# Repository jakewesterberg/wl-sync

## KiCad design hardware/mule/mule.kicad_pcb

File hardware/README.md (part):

# wl-sync breakout PCB

KiCad sources for the sync-box breakout board: a 2U rack-mount mixed-signal hub that sits
between the behavioural task PC, the sync-box module, the recording NI card, and the Intan RHS
amplifier. Every signal that crosses between those devices terminates on this board, is
conditioned once, and is fanned out — so a rig is reproducible from the board rather than from
hand wiring. "Sync-box module" is deliberately not a single product name: the module carries a
BCM2712 SoC and RP1 I/O controller either way, so its GPIO map and pinout are identical whether
it ships as a Raspberry Pi 5 or as a Compute Module 5 (Lite) on the official CM5 IO Board — the
choice between the two is a floorplan/placement decision this repository's own sources do not
yet lock in, not an electrical one.

Full design rationale, the signal contract, the grounding scheme, and the fabrication schedule
live in [`docs/superpowers/specs/2026-08-13-syncbox-breakout-pcb-design.md`](../docs/superpowers/specs/2026-08-13-syncbox-breakout-pcb-design.md).
The implementation plan (task breakdown, net naming convention, file layout) is at
[`docs/superpowers/plans/2026-08-13-breakout-pcb.md`](../docs/superpowers/plans/2026-08-13-breakout-pcb.md).
This repository is public: documentation here states electrical and mechanical facts and
tooling instructions only, and reproduces no text from either linked document's private source
material.

## Settled facts (record kept here, 2026-08-15)

Three facts a rig operator or firmware author needs and should not have to re-derive from the
schematic or the private spec:

- **The two photodiode comparator channels have distinct, fixed roles.** `A_PD1` watches the
  **task patch** — the stimulus-onset signal a behavioural task draws to cue an event.
  `A_PD2` watches the **flip patch**, a corner region of the display that alternates every
  refresh, making it a frame clock. Both reach the recorders as a digital edge through their
  own comparator (`PD1_COMP`/`PD2_COMP`) as well as an analog copy; the comparator lines carry
  the timing, the analog copies carry waveform and intensity.
- **The default eight analog channels Intan receives** (of the 16 sources this board carries;
  Intan's own ceiling is 8, and which eight is a mux setting, not a copper fact — see the
  ADG1206 mux truth table below): `A_PD1`, `A_EYE_LX`, `A_EYE_LY`, `A_EYE_LP`, `A_JOY_X`,
  `A_JOY_Y`, `A_MIC`, `A_ACC`. One complete eye (left, position + pupil) rather than partial
  data from both; the six eye channels are the first candidates to drop if a different set is
  ever needed, since they have an authoritative record on the eye-tracker PC independent of
  this board — the photodiode, joystick, accelerometer, and microphone channels do not.
- **MonkeyLogic's `RewardPolarity` setting must be `HIGH` to match this board.** This board's
  reward-commanded input (`RWD_CMD`) is active-HIGH by design (idle-LOW, pulses HIGH on
  delivery — the same convention every other event line on this board uses, and the polarity
  the reward-OR gate's own same-polarity structural check assumes and enforces on the
  debounced-button side). `RewardPolarity` is a MonkeyLogic Main Menu setting provided so a
  rig can match relays that trigger on sinking instead — it is a configuration to set for this
  board, never an unknown to discover at commissioning time.

## Two tracks

- **`hardware/mule/`** — the event-path mule. A small, fast board carrying only the 17-line
  event-code path plus one instance of each level-shift and isolation stage the full board
  reuses. It exists to reach the bench while the breakout board is still in layout, so the
  level-shifting and optocoupler topology gets validated against real hardware early enough to
  revise the sheets that depend on it.
- **`hardware/breakout/`** — the breakout board itself. A root sheet plus one hierarchical sheet
  per functional block (power, task-PC digital, Pi interface, analog front end, analog-to-NI,
  mux-to-Intan, comparators, opto-to-NI, opto-to-Intan, USB/I²C control).

As of this commit, `hardware/mule/` carries a generated schematic (`mule.kicad_sch`, produced
by `hardware/gen/gen_mule.py`) and a generated, placed-but-unrouted board (`mule.kicad_pcb`,
produced by `hardware/gen/gen_mule_pcb.py`) — see `hardware/mule/floorplan.md` for the
placement rationale and the constraints a router must respect. `hardware/breakout/` carries
the root sheet (`breakout.kicad_sch`, produced by `hardware/gen/gen_breakout.py`) plus two
populated child sheets so far: `sheets/power.kicad_sch` (produced by
`hardware/gen/gen_breakout_power.py`, Task 7) — the 5-position analog/logic inlet (widened
from 4 pins at Task 7 fix round 1, see below), the +3V3 logic rail regulated from +5V, and
the one isolated ±12V supply the other nine sheets draw power from; see that generator's own
module docstring and `check_breakout_power_netlist.py` for the design and its verification.
Task 7 fix round 1 (task-7-report.md's "Fix round 1") corrected two defects found in
review: the +5V rail was undersized regulating it down from +12V on board (fixed by
bringing +5V in directly from the external supply on a fifth inlet pin instead, budgeted
for 400mA), and the child sheet's own component `(instances (path ...))` ancestor chain was
self-referential rather than the real root+sheet-symbol chain a nested sheet needs (fixed
generically in `kicad_sch.py`, not just for this one sheet — see the "KiCad gotchas" entry
below). Task 7 fix round 2 (task-7-report.md's "Fix round 2") replaced the inlet
**connector** itself — not its electrical design — after a reviewer confirmed the mini-DIN
footprints modelled an evenly-spaced ring the real Same Sky MD-40SN/MD-50SN datasheet's own
diagrams contradict, and that both parts are discontinued besides. The inlet is now a
5-position, IEC 61076-2-101 A-coded, keyed, screw-locking M12 connector (Amphenol LTW
M12A-05PFFP-SF8001, current production, 811 units in stock directly confirmed at DigiKey)
— see "Custom connector footprints" below for the full selection rationale and
per-dimension sourcing.

**Panel-instrumentation task (2026-08-15), Change D — four of the five "things a rack
instrument needs that this one lacked" (spec §9.8) land on this sheet** (the fifth,
the barcode heartbeat LED, is on `pi-interface.kicad_sch` — see that sheet's own
paragraph below):

- **Chassis earth stud (`J56`):** a `Connector_Generic:Conn_01x01` on footprint
  `MountingHole:MountingHole_3.2mm_M3_Pad` — an M3-clearance hole *with* a connected
  copper pad, simultaneously the mechanical mount and the electrical land the
  cage-to-rack bond (spec §5.6) needs somewhere to terminate. Carries a new net,
  `CHASSIS_GND`, joined to `DGND` at exactly one net tie (`NT3`) — mirroring `NT2`'s own
  `FAN_RTN`↔`DGND` treatment exactly, so the stud reaches the board's single star point
  transitively (through `NT3` then `NT1`/`NT2`), never by a second, competing path.
- **Power-good LED per rail (`D40`/`D41`/`D42`, +12V/−12V/+5V):** series resistor + LED
  between each rail and its own local ground reference (`AGND` for ±12V, `DGND` for
  +5V) — `−12V`'s own pair is mirrored (resistor/anode on the `AGND` side, cathode on
  `−12V`), the identical reasoning `D2`'s own reverse-polarity-diode orientation already
  uses. ~4.5 mA target each (`R192`/`R193` = 2.2k, `R194` = 680R) — negligible against
  any rail's own real budget.
- **Rail test points (`TP1`–`TP7`):** one `Connector:TestPoint` per voltage rail (+12V,
  −12V, +5V, +3V3, ISO_P12, ISO_N12) *plus one on `INTAN_GND`* — the isolated domain's
  own reference, without which `ISO_P12`/`ISO_N12` cannot actually be measured at all
  (`INTAN_GND` is galvanically separate from `AGND`/`DGND`, spec §5.3/§5.5). `AGND`/
  `DGND` themselves are not given dedicated test points — already trivially probable at
  any of this sheet's own many ground pads.
- **Main input fusing (`F2`/`F3`/`F4`, +12V/−12V/+5V):** "the fans already have a
  polyfuse; these did not" (spec §9.8). Placed upstream of each rail's own existing
  reverse-polarity diode (`D1`/`D2`/`D3`) — their own raw-side net renamed `*_FUSED`
  (e.g. `P12_RAW` → `F2` → `P12_FUSED` → `D1` → `+12V`), `D1`–`D3` themselves keeping
  their existing references unchanged. `F2`/`F3` are Littelfuse `1206L050/15YR`
  (500 mA hold / 1 A trip / **15 V** max), the same real part as the fan feed's `F1`.

  **`F4` is a different part — finding M7, 2026-08-16.** The sizing note that used to
  sit here called +5V's 1.25× hold margin "tighter than usual but accepted, because a
  main-input fuse guards against a gross fault". That reasoning does not survive finding
  F1: the +5 V rail now carries **392 mA typ / 495 mA max**, and a `1206L050` holds only
  ~0.44 A at this chassis's 35 °C ambient. It would have tripped in **normal operation**,
  not on a fault. `F4` is now **`1206L110-C`** — 1.10 A hold / 2.20 A trip, ~0.97 A
  derated at 35 °C, a 1.97× margin.

  **Its V_max is 6 Vdc, not 15, and that is not interchangeable.** In the 1206L series
  the elevated-voltage variants exist only at the two lowest hold currents; everything at
  0.75 A and above is a +5 V-rail part. So `F4` could move and `F1`/`F2`/`F3` cannot —
  **0.50 A is the largest 1206L hold current available to a 12 V rail at all**, which is
  also why M7's "0.75 A recommended" for the fan feed cannot be satisfied in this series.
  Do not consolidate the two values back into one.

- **The fan branch is parallel to the main +12 V branch, not downstream of it (finding
  F7, 2026-08-16).** `F1` used to be fed from `+12V`, which put it in series with `F2` at
  identical ratings — and two identical parts in series have no selectivity at all: a fan
  fault at 0.9 A is below `F1`'s trip but over `F2`'s hold, so **`F2` could open first and
  kill the analog rails to protect the fans.** The fan feed now taps `P12_RAW` directly,
  with its own reverse-polarity Schottky (`D44`, `SS14`) since it no longer sits behind
  `D1`:

  ```
  J1.1 → P12_RAW ─┬─ [F2] → P12_FUSED   → [D1]  → +12V      (main, 97–121 mA)
                  └─ [F1] → FAN_12V_RAW → [D44] → FAN_12V   (fans, 240 mA)
  ```

- **Every panel output now sits behind series resistance, and no logic output drives more
  than one connector (findings F4 and M3, 2026-08-16).** `CAM_TRIG_BEH` drove **four** BNCs
  from a single `SN74AHCT541` output: four parallel coax runs present Z₀/4 ≈ 12.5 Ω, so the
  initial edge drew roughly **118 mA against the part's 25 mA per-output absolute
  maximum** — brief, but on every edge for the life of the board, and with no source
  termination the cameras could see reflections and double-trigger. Each trigger now has its
  own buffer channel (`CAM_TRIG_BEH1`–`4`, the extra three on `U74`) and its own **47 Ω**.
  They still share one trigger *rate* via `CAM_TRIG_BEH_RAW`; they no longer share a driver.

  M3 named **six** bare panel outputs. There were **eleven** — the five *digital* Intan
  output BNCs sat directly on the ACSL-6xx0 output pins too. (The finding's "every Intan
  output has a series resistor" is true of the *analog* outputs, which each sit behind
  100 Ω, and was not true of the digital ones.) All eleven now carry series resistance:
  47 Ω on the five camera triggers, 100 Ω on `J6` and the five Intan BNCs. The extra five
  were found by the checker written *for* M3, which is stated over every panel output rather
  than over the six nets the finding lists.

  `tests/hardware/test_netlist.py` derives series-ness from **topology** — by testing
  whether removing one fuse disconnects another from the supply inlet — rather than from
  net names. That matters: the audit's own published fix for this named `P12_FUSED` as
  "upstream of `F2`" when it is `F2`'s *output*, which would have fixed nothing and
  removed the fan branch's reverse-polarity protection as well. ±12V's own real total draw was **not** independently characterized
  to the same precision (it sums a computed IH1215D input-current estimate, the fan
  feed, and an uncharacterized contribution from the ±12V-referenced op-amp stages on
  `analog-frontend.kicad_sch`/`analog-ni.kicad_sch`) — flagged explicitly for bench
  confirmation before treating the margin as final, the same "tell me if it doesn't fit"
  posture this file's own +3V3/NI-budget notes already use elsewhere. A higher-current,
  higher-voltage PPTC (Bourns `MF-SM` series) was evaluated and **rejected**: its own
  datasheet states hand soldering is not recommended, which would add a third accepted
  hand-solderability exception beyond the two spec §10.1 documents (`MCP4728`, the two
  exposed-pad regulators) — see `_place_inlet()`'s own docstring for the full account.

And `sheets/taskpc-digital.kicad_sch` (produced by
`hardware/gen/gen_breakout_taskpc_digital.py`, Task 8) — both task-PC MDR68 connectors
(Connector 1 wired with the 23 digital lines; Connector 0 carries its 9 task-PC analog
channels plus the AISENSE-to-AGND tie, everything else no_connect pending Task 10's own
front-end/buffer circuitry), the 19-channel inbound protected/buffered path (100Ω +
BAT54S clamp per channel, high side +5V never +3V3, fanned out in parallel to a 3.3V
`SN74LVC541APW` bank and a 5V `SN74AHCT541PW` `_BUF` bank for Task 11's optocouplers), the
4-channel outbound path, and the reward OR (`74HCT32` + a single debounced `74HCT14`
Schmitt inverter); see that generator's own module docstring and
`check_taskpc_digital_netlist.py` for the design and its verification. Task 8 is this
project's first case of two REAL sibling child sheets coexisting, which surfaced a
cross-sheet reference-collision gotcha `kicad_sch.py` needed a generic fix for — see the
"KiCad gotchas" entry below.

**Task 8 fix round 1** (`task-8-report.md`'s own "Fix round 1") corrected three findings
raised by the implementer's own report, all disclosed concerns the implementer was right
to flag: (1) **critical** — the reward-OR debounce stage placed a `74HCT14` Schmitt
*pair* (task-8-brief.md's own literal, incorrect text); two series inversions cancel, so
the debounced button would idle HIGH into an OR gate against an active-HIGH `RWD_CMD`,
asserting `RWD_DLVR` continuously. Fixed to a *single* inverter (idle-LOW/active-HIGH,
matching an OR gate's actual requirement); `RWD_CMD`'s assumed active-HIGH polarity is
now stated explicitly on-sheet, and the checker asserts the OR's two inputs are
same-polarity. (2) Connector 1's physical MDR68 pin assignment was this sheet's own
sequential guess; it is now sourced from NI's own "X Series User Manual" (National
Instruments 370784K-01, May 2019), Figure A-5 "NI PCIe-6323/6343 Pinout" — the task PC's
own card — for every P0.x and D GND position. (3) Connector 0's 9 task-PC analog channels
(`A_EYE_LX_TPC` etc., plan.md's own net-naming table) and its AISENSE-to-AGND tie are now
wired on this sheet (the same physical-pin source above), since only the file that places
a symbol can label its pins and Task 10 does not exist yet. See `task-8-report.md`'s own
"Fix round 1" section for the full retrieval/verification method and the reasoning behind
each fix.

**Panel-instrumentation task (2026-08-15), Changes A+B — manual reward becomes a one-shot,
and the three reward positions become real connectors.** Both changes land entirely on
`taskpc-digital.kicad_sch`'s own reward circuit:

- **One-shot (Change A):** a Nexperia `74HCT123D` dual retriggerable monostable (`U69`)
  now sits between the debounce inverter's own output (`RWD_BTN_DEB`) and the reward-OR
  gate's second input (`RWD_BTN_PULSE`, the one-shot's own `Q`) — every hand-delivered
  reward gets a fixed **~199 ms** pulse regardless of how long the button is held (spec
  §3.1). `Rext=442k` (E96) + `Cext=1µF` (`R191`/`C149`, both minted out of band), K=0.45 at
  VCC=5.0V (the part's own datasheet, Table 10) → tW = 0.45×442×1,000,000 ns ≈ 198.9 ms,
  cross-checked against that same table's own measured example (100 nF/10 kΩ → 450 µs;
  the formula predicts exactly that). Real part, not TI: TI's own `CD74HCT123M`/`MT` is
  obsolete; Nexperia's `74HCT123D` is current production, thousands of units in stock at
  DigiKey/Mouser/TME (checked 2026-08-15). Pin map verified pin-by-pin against
  Philips/Nexperia's own Rev. 03 (11 May 2004) datasheet, Table 3/Fig. 5, cross-checked
  against KiCad's own stock `74xx:74HCT123` library entry — see
  `gen_breakout_taskpc_digital.py`'s own `place_reward_oneshot()` docstring for the full
  account, including why the part's own retriggerable behaviour does not undermine "fixed
  duration regardless of hold time" (a continuous hold produces exactly one trigger edge).
  The debounce capacitor changes from 100 nF to **1 µF** (10 kΩ × 1 µF = 10 ms, spec
  §3.1), covering both switch bounce and the longer remote-BNC cable run's own
  connector-mating transient.
- **Real connectors (Change B):** the manual reward button (`J4`) is now
  `Switch:SW_Push` on a real panel/chassis-mount momentary-pushbutton footprint
  (`Button_Switch_THT:SW_PUSH-12mm`), **recessed** per spec §3.1 ("so a sleeve or cable
  cannot dispense fluid"). The remote reward jack (`J5`) and reward-driver output (`J6`)
  are both real BNCs (`Connector:Conn_Coaxial` / `Connector_Coaxial:BNC_PanelMountable_
  Vertical` — the same footprint the camera-trigger BNCs already use), replacing generic
  `Connector_Generic:Conn_01x02` placeholders. **This removes the 3.5 mm TRS from the
  design entirely** — `J5` was its last use (spec §9.6): a BNC's own center pin cannot
  transiently short to the shield while mating the way a TRS tip/ring/sleeve does sliding
  past a jack's own switching contacts, so plugging in the handheld remote cannot itself
  fire a reward, and the coupling locks. No TRS footprint or symbol exists anywhere on the
  board any more (confirmed by grep across every generator and committed sheet, and
  asserted directly by `check_taskpc_digital_netlist.py`'s own whole-board footprint scan,
  with a negative control). `J4`/`J5`/`J6` keep their existing reference numbers — the
  symbol/footprint/value changed at their own existing call sites, nothing moved.

**A real ref_start hazard, found and fixed while making these changes, not before:**
`taskpc-digital.kicad_sch`'s own `build()` used to re-derive its reference-counter seed by
reading `power.kicad_sch`'s *current* committed text on every regeneration
(`find_max_refs(POWER_SCH.read_text())`). That was safe until power.kicad_sch's own
fan-header addendum (spec §9.5) minted `J52`–`J55`/`C147`/`C148` out of band, *after*
taskpc-digital.kicad_sch was last generated — from that point on, simply regenerating
taskpc-digital.kicad_sch again (even with no source changes at all) would have silently
**renumbered every one of its own existing J- and C-prefixed components**, since the
recomputed seed jumps from the sheet's own small pre-fan-header baseline straight to
power.kicad_sch's own new, much larger maxima. Confirmed empirically before fixing it: an
unmodified copy of the generator, run against the *current* power.kicad_sch, reproduced
`R24`/`D22`/`U13` exactly (genuinely unaffected) but `J60`/`C158` instead of the
historically-correct `J6`/`C31`. Fixed by **pinning** `ref_start` to the exact historical
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
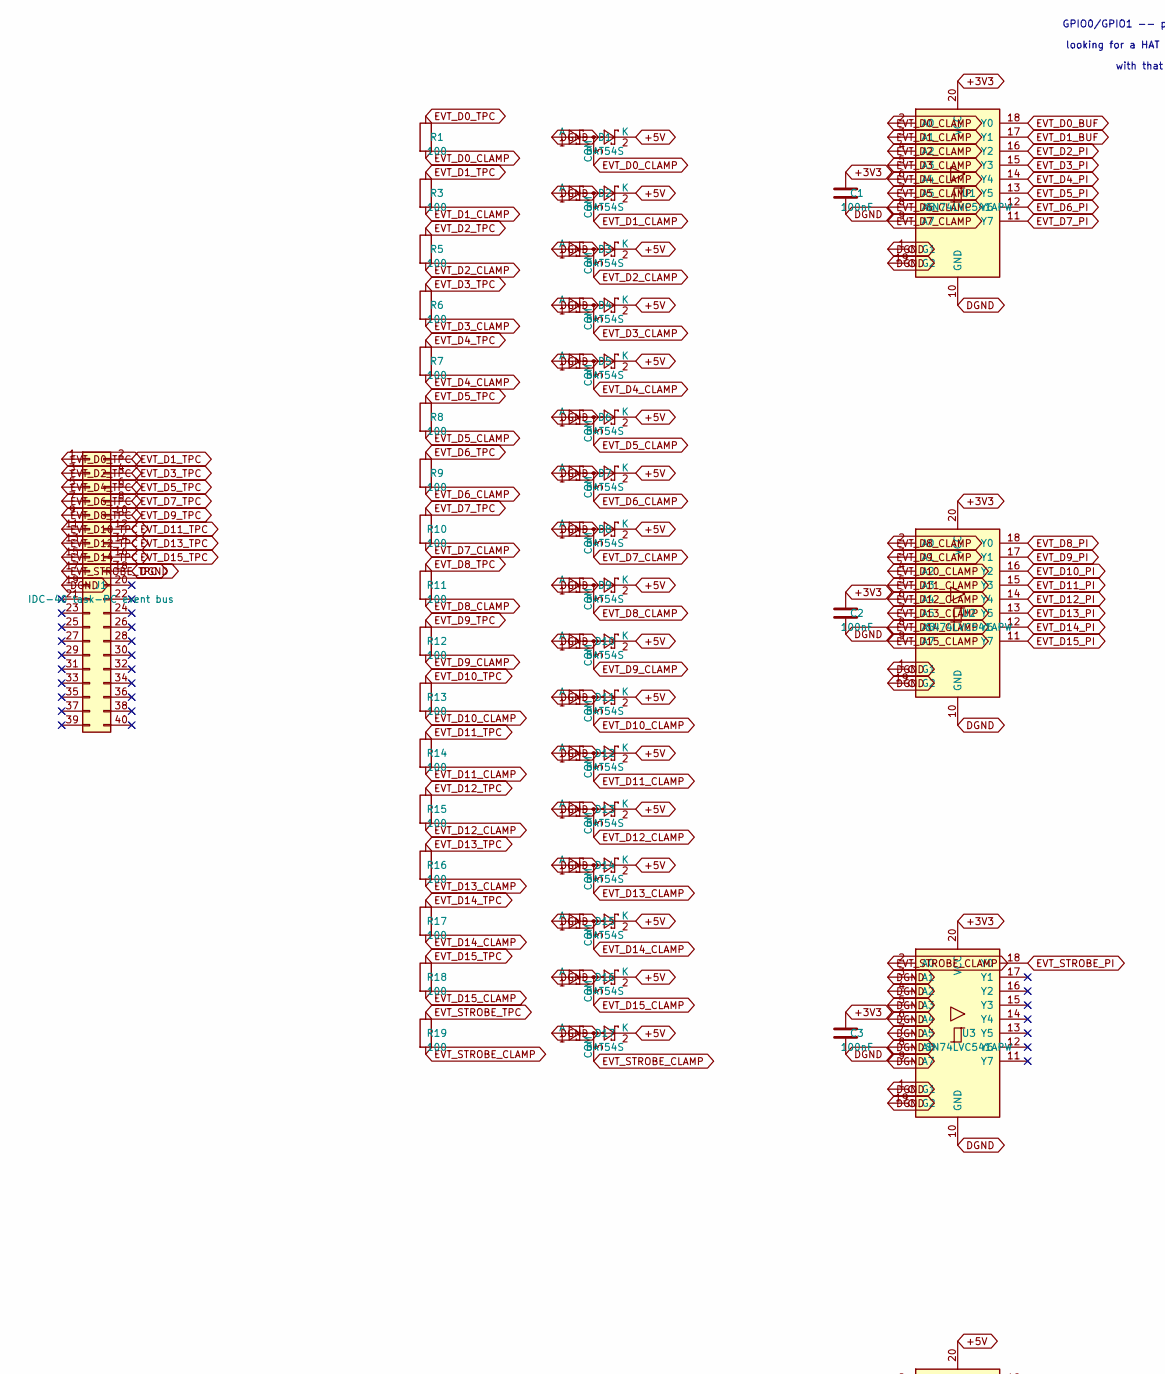
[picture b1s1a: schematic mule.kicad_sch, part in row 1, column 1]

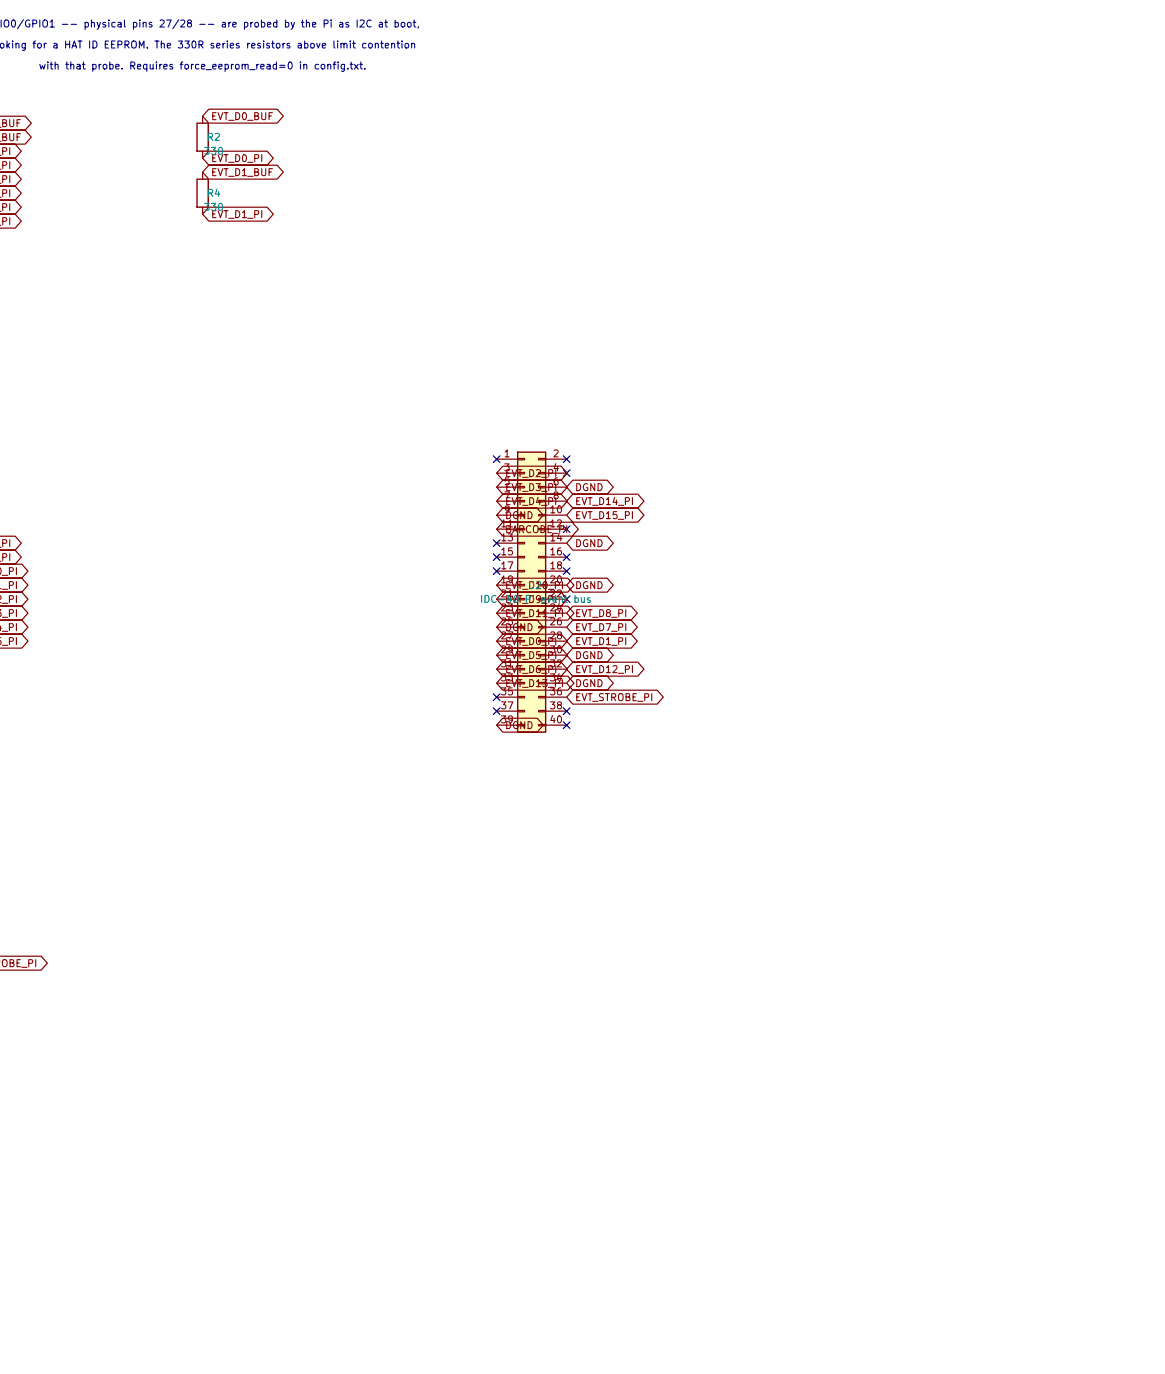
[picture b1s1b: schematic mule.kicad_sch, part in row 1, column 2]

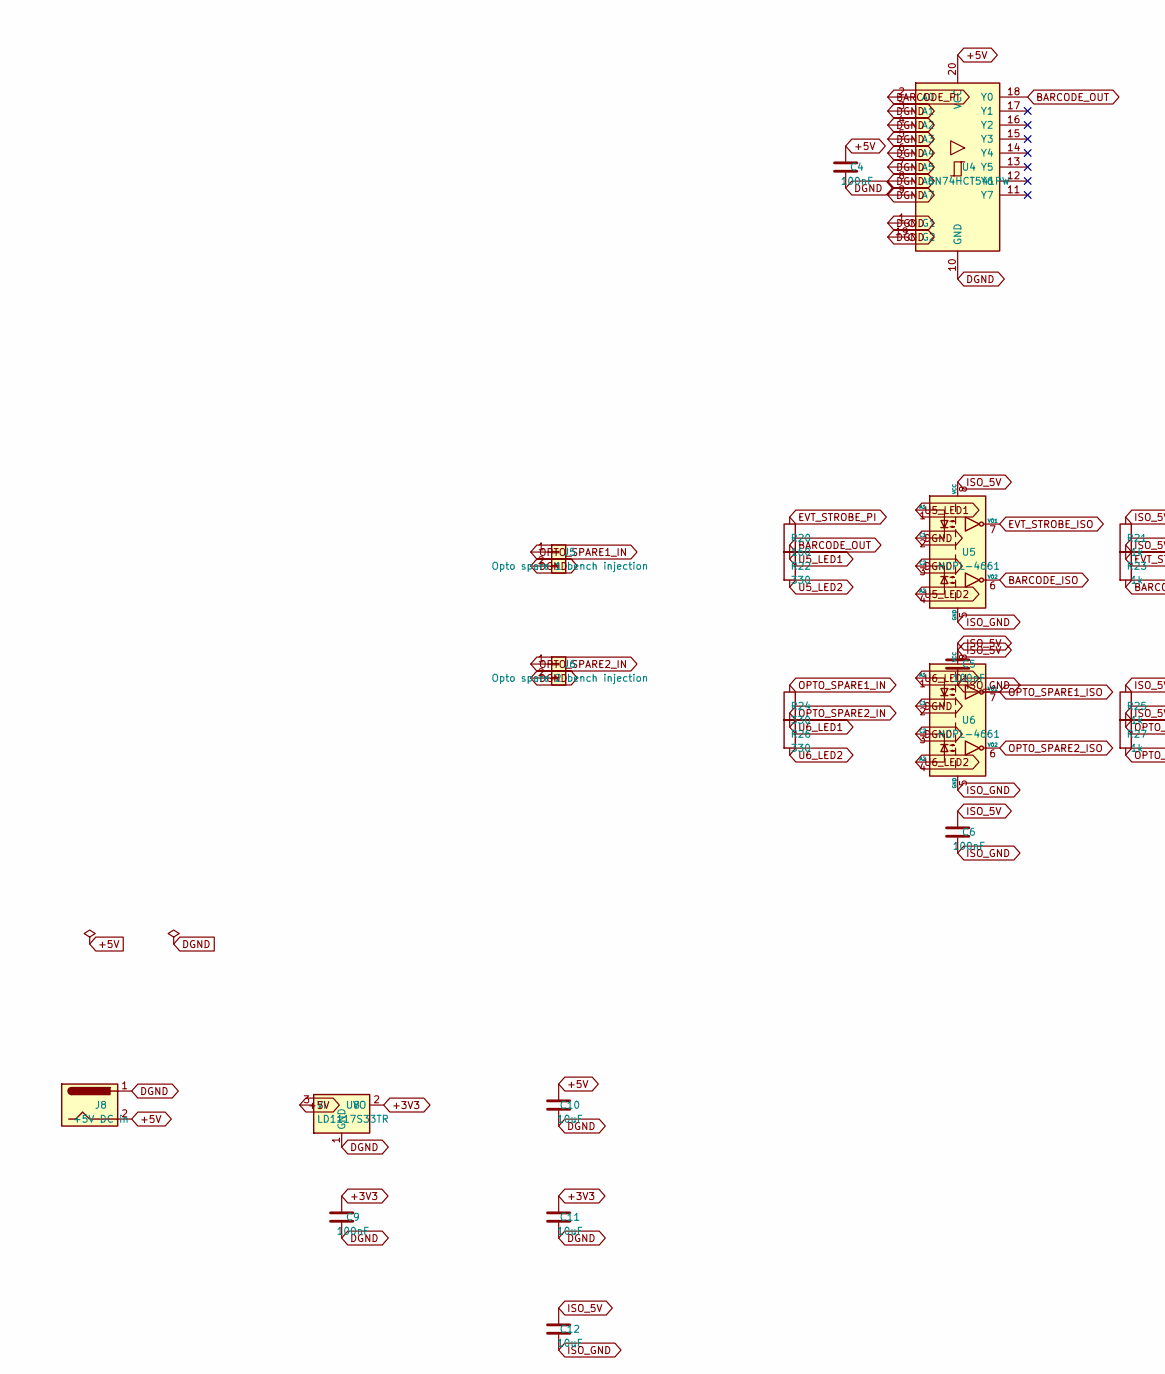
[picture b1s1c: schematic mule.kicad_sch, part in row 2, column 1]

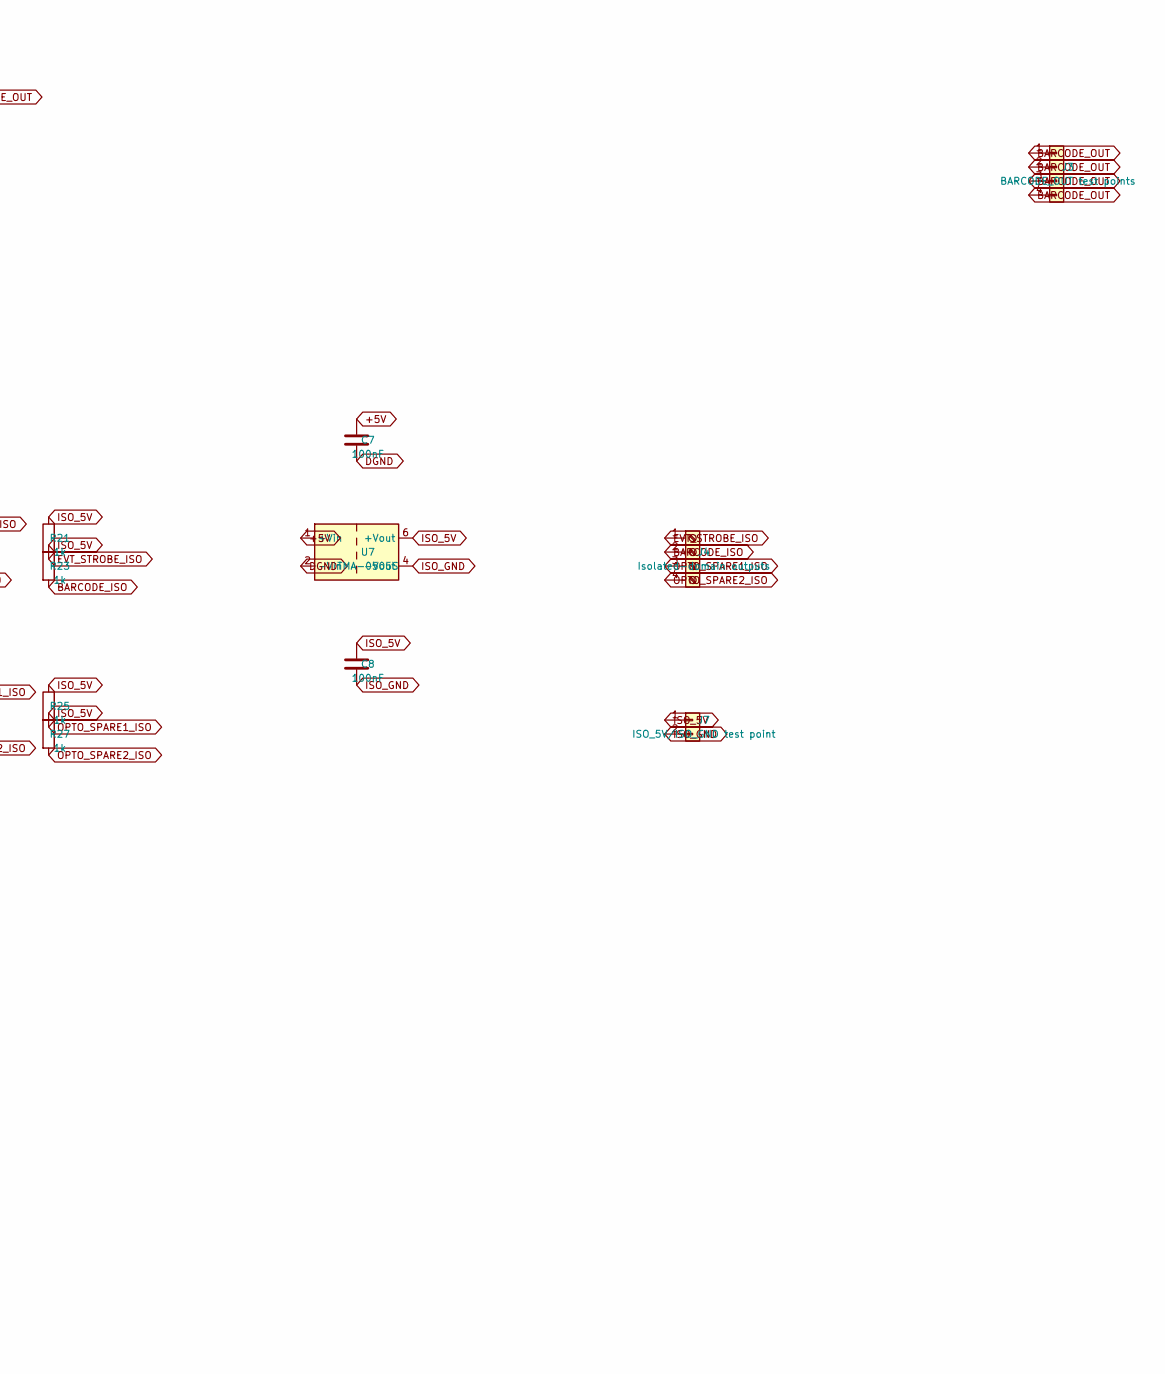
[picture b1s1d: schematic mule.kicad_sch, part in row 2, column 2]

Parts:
C1, C2, C3, C4, C5, C6, C7, C8, C9: 100nF; C_0603_1608Metric
C10, C11, C12: 10uF; C_0805_2012Metric
D1, D2, D3, D4, D5, D6, D7, D8, D9, D10, D11, D12, D13, D14, D15, D16, D17: BAT54S; SOT-23
J1: IDC-40 task-PC event bus; PinHeader_2x20_P2.54mm_Vertical
J2: IDC-40 Pi event bus; PinHeader_2x20_P2.54mm_Vertical
J3: BARCODE_OUT test points; PinHeader_1x04_P2.54mm_Vertical
J4: Isolated-domain outputs; TerminalBlock_Phoenix_MKDS-1,5-4_1x04_P5.00mm_Horizontal
J5: Opto spare 1 bench injection; PinHeader_1x02_P2.54mm_Vertical
J6: Opto spare 2 bench injection; PinHeader_1x02_P2.54mm_Vertical
J7: ISO_5V/ISO_GND test point; PinHeader_1x02_P2.54mm_Vertical
J8: +5V DC in; BarrelJack_CUI_PJ-102AH_Horizontal
R1, R3, R5, R6, R7, R8, R9, R10, R11, R12, R13, R14, R15, R16, R17, R18, R19: 100; R_0603_1608Metric
R2, R4, R22, R24, R26: 330; R_0603_1608Metric
R20: 160; R_0603_1608Metric
R21, R23, R25, R27: 1k; R_0603_1608Metric
U1, U2, U3: SN74LVC541APW; Texas_PW0020A_TSSOP-20_4.4x6.5mm_P0.65mm
U4: SN74HCT541PW; Texas_PW0020A_TSSOP-20_4.4x6.5mm_P0.65mm
U5, U6: HCPL-4661; DIP-8_W7.62mm
U7: TMA-0505S; Converter_DCDC_TRACO_TMA-05xxS_12xxS_Single_THT
U8: LD1117S33TR; SOT-223-3_TabPin2

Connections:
+3V3: C1.1, C2.1, C3.1, C9.1, C11.1, U1.20 (VCC), U2.20 (VCC), U3.20 (VCC), U8.2 (VO)
BARCODE_ISO: J4.2, R23.2, U5.6 (VO2)
BARCODE_OUT: J3.1, J3.2, J3.3, J3.4, R22.1, U4.18 (Y0)
BARCODE_PI: J2.11, U4.2 (A0)
EVT_D0_BUF: R2.1, U1.18 (Y0)
EVT_D0_CLAMP: D1.3 (COM), R1.2, U1.2 (A0)
EVT_D0_PI: J2.27, R2.2
EVT_D0_TPC: J1.1, R1.1
EVT_D1_BUF: R4.1, U1.17 (Y1)
EVT_D1_CLAMP: D2.3 (COM), R3.2, U1.3 (A1)
EVT_D1_PI: J2.28, R4.2
EVT_D1_TPC: J1.2, R3.1
EVT_D2_CLAMP: D3.3 (COM), R5.2, U1.4 (A2)
EVT_D2_PI: J2.3, U1.16 (Y2)
EVT_D2_TPC: J1.3, R5.1
EVT_D3_CLAMP: D4.3 (COM), R6.2, U1.5 (A3)
EVT_D3_PI: J2.5, U1.15 (Y3)
EVT_D3_TPC: J1.4, R6.1
EVT_D4_CLAMP: D5.3 (COM), R7.2, U1.6 (A4)
EVT_D4_PI: J2.7, U1.14 (Y4)
EVT_D4_TPC: J1.5, R7.1
EVT_D5_CLAMP: D6.3 (COM), R8.2, U1.7 (A5)
EVT_D5_PI: J2.29, U1.13 (Y5)
EVT_D5_TPC: J1.6, R8.1
EVT_D6_CLAMP: D7.3 (COM), R9.2, U1.8 (A6)
EVT_D6_PI: J2.31, U1.12 (Y6)
EVT_D6_TPC: J1.7, R9.1
EVT_D7_CLAMP: D8.3 (COM), R10.2, U1.9 (A7)
EVT_D7_PI: J2.26, U1.11 (Y7)
EVT_D7_TPC: J1.8, R10.1
EVT_D8_CLAMP: D9.3 (COM), R11.2, U2.2 (A0)
EVT_D8_PI: J2.24, U2.18 (Y0)
EVT_D8_TPC: J1.9, R11.1
EVT_D9_CLAMP: D10.3 (COM), R12.2, U2.3 (A1)
EVT_D9_PI: J2.21, U2.17 (Y1)
EVT_D9_TPC: J1.10, R12.1
EVT_D10_CLAMP: D11.3 (COM), R13.2, U2.4 (A2)
EVT_D10_PI: J2.19, U2.16 (Y2)
EVT_D10_TPC: J1.11, R13.1
EVT_D11_CLAMP: D12.3 (COM), R14.2, U2.5 (A3)
EVT_D11_PI: J2.23, U2.15 (Y3)
EVT_D11_TPC: J1.12, R14.1
EVT_D12_CLAMP: D13.3 (COM), R15.2, U2.6 (A4)
EVT_D12_PI: J2.32, U2.14 (Y4)
EVT_D12_TPC: J1.13, R15.1
EVT_D13_CLAMP: D14.3 (COM), R16.2, U2.7 (A5)
EVT_D13_PI: J2.33, U2.13 (Y5)
EVT_D13_TPC: J1.14, R16.1
EVT_D14_CLAMP: D15.3 (COM), R17.2, U2.8 (A6)
EVT_D14_PI: J2.8, U2.12 (Y6)
EVT_D14_TPC: J1.15, R17.1
EVT_D15_CLAMP: D16.3 (COM), R18.2, U2.9 (A7)
EVT_D15_PI: J2.10, U2.11 (Y7)
EVT_D15_TPC: J1.16, R18.1
EVT_STROBE_CLAMP: D17.3 (COM), R19.2, U3.2 (A0)
EVT_STROBE_ISO: J4.1, R21.2, U5.7 (VO1)
EVT_STROBE_PI: J2.36, R20.1, U3.18 (Y0)
EVT_STROBE_TPC: J1.17, R19.1
ISO_5V: C5.1, C6.1, C8.1, C12.1, J7.1, R21.1, R23.1, R25.1, R27.1, U5.8 (VCC), U6.8 (VCC), U7.6 (+Vout)
ISO_GND: C5.2, C6.2, C8.2, C12.2, J7.2, U5.5 (GND), U6.5 (GND), U7.4 (-Vout)
OPTO_SPARE1_IN: J5.1, R24.1
OPTO_SPARE1_ISO: J4.3, R25.2, U6.7 (VO1)
OPTO_SPARE2_IN: J6.1, R26.1
OPTO_SPARE2_ISO: J4.4, R27.2, U6.6 (VO2)
U5_LED1: R20.2, U5.1 (A1)
U5_LED2: R22.2, U5.4 (A2)
U6_LED1: R24.2, U6.1 (A1)
U6_LED2: R26.2, U6.4 (A2)

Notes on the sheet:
looking for a HAT ID EEPROM. The 330R series resistors above limit contention
with that probe. Requires force_eeprom_read=0 in config.txt.
GPIO0/GPIO1 -- physical pins 27/28 -- are probed by the Pi as I2C at boot,

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
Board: 2 copper layers, 72 parts (0 on the bottom side), 70 nets, no tracks yet.

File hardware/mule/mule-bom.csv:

"Reference","Value","Footprint","MPN","Qty"
"C1","100nF","Capacitor_SMD:C_0603_1608Metric","",""
"C2","100nF","Capacitor_SMD:C_0603_1608Metric","",""
"C3","100nF","Capacitor_SMD:C_0603_1608Metric","",""
"C4","100nF","Capacitor_SMD:C_0603_1608Metric","",""
"C5","100nF","Capacitor_SMD:C_0603_1608Metric","",""
"C6","100nF","Capacitor_SMD:C_0603_1608Metric","",""
"C7","100nF","Capacitor_SMD:C_0603_1608Metric","",""
"C8","100nF","Capacitor_SMD:C_0603_1608Metric","",""
"C9","100nF","Capacitor_SMD:C_0603_1608Metric","",""
"C10","10uF","Capacitor_SMD:C_0805_2012Metric","",""
"C11","10uF","Capacitor_SMD:C_0805_2012Metric","",""
"C12","10uF","Capacitor_SMD:C_0805_2012Metric","",""
"D1","BAT54S","Package_TO_SOT_SMD:SOT-23","",""
"D2","BAT54S","Package_TO_SOT_SMD:SOT-23","",""
"D3","BAT54S","Package_TO_SOT_SMD:SOT-23","",""
"D4","BAT54S","Package_TO_SOT_SMD:SOT-23","",""
"D5","BAT54S","Package_TO_SOT_SMD:SOT-23","",""
"D6","BAT54S","Package_TO_SOT_SMD:SOT-23","",""
"D7","BAT54S","Package_TO_SOT_SMD:SOT-23","",""
"D8","BAT54S","Package_TO_SOT_SMD:SOT-23","",""
"D9","BAT54S","Package_TO_SOT_SMD:SOT-23","",""
"D10","BAT54S","Package_TO_SOT_SMD:SOT-23","",""
"D11","BAT54S","Package_TO_SOT_SMD:SOT-23","",""
"D12","BAT54S","Package_TO_SOT_SMD:SOT-23","",""
"D13","BAT54S","Package_TO_SOT_SMD:SOT-23","",""
"D14","BAT54S","Package_TO_SOT_SMD:SOT-23","",""
"D15","BAT54S","Package_TO_SOT_SMD:SOT-23","",""
"D16","BAT54S","Package_TO_SOT_SMD:SOT-23","",""
"D17","BAT54S","Package_TO_SOT_SMD:SOT-23","",""
"J1","IDC-40 task-PC event bus","Connector_PinHeader_2.54mm:PinHeader_2x20_P2.54mm_Vertical","",""
"J2","IDC-40 Pi event bus","Connector_PinHeader_2.54mm:PinHeader_2x20_P2.54mm_Vertical","",""
"J3","BARCODE_OUT test points","Connector_PinHeader_2.54mm:PinHeader_1x04_P2.54mm_Vertical","",""
"J4","Isolated-domain outputs","TerminalBlock_Phoenix:TerminalBlock_Phoenix_MKDS-1,5-4_1x04_P5.00mm_Horizontal","",""
"J5","Opto spare 1 bench injection","Connector_PinHeader_2.54mm:PinHeader_1x02_P2.54mm_Vertical","",""
"J6","Opto spare 2 bench injection","Connector_PinHeader_2.54mm:PinHeader_1x02_P2.54mm_Vertical","",""
"J7","ISO_5V/ISO_GND test point","Connector_PinHeader_2.54mm:PinHeader_1x02_P2.54mm_Vertical","",""
"J8","+5V DC in","Connector_BarrelJack:BarrelJack_CUI_PJ-102AH_Horizontal","",""
"R1","100","Resistor_SMD:R_0603_1608Metric","",""
"R2","330","Resistor_SMD:R_0603_1608Metric","",""
"R3","100","Resistor_SMD:R_0603_1608Metric","",""
"R4","330","Resistor_SMD:R_0603_1608Metric","",""
"R5","100","Resistor_SMD:R_0603_1608Metric","",""
"R6","100","Resistor_SMD:R_0603_1608Metric","",""
"R7","100","Resistor_SMD:R_0603_1608Metric","",""
"R8","100","Resistor_SMD:R_0603_1608Metric","",""
"R9","100","Resistor_SMD:R_0603_1608Metric","",""
"R10","100","Resistor_SMD:R_0603_1608Metric","",""
"R11","100","Resistor_SMD:R_0603_1608Metric","",""
"R12","100","Resistor_SMD:R_0603_1608Metric","",""
"R13","100","Resistor_SMD:R_0603_1608Metric","",""
"R14","100","Resistor_SMD:R_0603_1608Metric","",""
"R15","100","Resistor_SMD:R_0603_1608Metric","",""
"R16","100","Resistor_SMD:R_0603_1608Metric","",""
"R17","100","Resistor_SMD:R_0603_1608Metric","",""
"R18","100","Resistor_SMD:R_0603_1608Metric","",""
"R19","100","Resistor_SMD:R_0603_1608Metric","",""
"R20","160","Resistor_SMD:R_0603_1608Metric","",""
"R21","1k","Resistor_SMD:R_0603_1608Metric","",""
"R22","330","Resistor_SMD:R_0603_1608Metric","",""
"R23","1k","Resistor_SMD:R_0603_1608Metric","",""
"R24","330","Resistor_SMD:R_0603_1608Metric","",""
"R25","1k","Resistor_SMD:R_0603_1608Metric","",""
"R26","330","Resistor_SMD:R_0603_1608Metric","",""
"R27","1k","Resistor_SMD:R_0603_1608Metric","",""
"U1","SN74LVC541APW","Package_SO:Texas_PW0020A_TSSOP-20_4.4x6.5mm_P0.65mm","",""
"U2","SN74LVC541APW","Package_SO:Texas_PW0020A_TSSOP-20_4.4x6.5mm_P0.65mm","",""
"U3","SN74LVC541APW","Package_SO:Texas_PW0020A_TSSOP-20_4.4x6.5mm_P0.65mm","",""
"U4","SN74HCT541PW","Package_SO:Texas_PW0020A_TSSOP-20_4.4x6.5mm_P0.65mm","",""
"U5","HCPL-4661","Package_DIP:DIP-8_W7.62mm","",""
"U6","HCPL-4661","Package_DIP:DIP-8_W7.62mm","",""
"U7","TMA-0505S","Converter_DCDC:Converter_DCDC_TRACO_TMA-05xxS_12xxS_Single_THT","",""
"U8","LD1117S33TR","Package_TO_SOT_SMD:SOT-223-3_TabPin2","",""

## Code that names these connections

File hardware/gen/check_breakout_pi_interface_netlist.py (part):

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
# This task's own net contract ("consumes ... from Task 8" / "Produces").
CONSUMED_CONTRACT_NETS = [f"EVT_D{i}_PI" for i in range(16)] + [
    "EVT_STROBE_PI", "RWD_CMD", "RWD_DLVR", "STIM_TRIG", "PD1_COMP", "PD2_COMP", "ACC_TRIG",
    # Produced on comparators.kicad_sch exactly as PD1_COMP/PD2_COMP/ACC_TRIG are.
    "CAM_FRAME_EYE", "CAM_FRAME_BEH",
]
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
def _find_header_ref(nets: dict[str, list[Node]]) -> str:
    """The RaspberryPi5_GPIO_Header instance's own reference, found by walking a net that
    can ONLY have a header pin on it besides Task 8's own driver (EVT_D2_PI: Task 8's
    SN74LVC541APW tri-state output + this sheet's own header pin, nothing else) and
    taking the "J"-prefixed one -- NOT by filtering on Value text (this symbol is placed
    with a human-readable description as its Value, e.g. "Sync-module 40-pin GPIO
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        )
    for pin in GND_PHYSICAL_PINS:
        check(
            pin_map.get(str(pin)) == "DGND",
            f"header physical pin {pin}: expected DGND (one of the 8 real GND "
            f"positions), found {pin_map.get(str(pin))!r}",
        )
    for pin in V3V3_PHYSICAL_PINS + V5_PHYSICAL_PINS:
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            f"two regulated supplies), found {pin_map.get(str(pin))!r}",
        )
    summary.append(
        f"All 8 GND pins land on DGND at their real physical positions {GND_PHYSICAL_PINS}; "
        f"all 4 power pins ({V3V3_PHYSICAL_PINS + V5_PHYSICAL_PINS}) and both spare GPIOs "
        f"{SPARE_GPIOS} are genuinely no-connect."
    )

    # --- GPIO0/GPIO1 series resistors: 330R each, bridging the received EVT_D{0,1}_PI
    # contract net to the LOCAL header-pin net -- boot-contention mitigation (spec Sec.4). ---
    for gpio, contract_net in ((0, "EVT_D0_PI"), (1, "EVT_D1_PI")):
        hdr_net = GPIO_NET_AT_PIN[gpio]
        check(contract_net in nets, f"missing net: {contract_net!r}")
        r_on_contract = [n for n in nets[contract_net] if n.ref.startswith("R")]
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        # what that control is for.
        hb_out_pin not in all_pins,
        f"{trig_buf}: BARCODE_HB's own output pin ({hb_out_pin}) collides with one of "
        f"BARCODE_PI/CAM_SYNC_EYE/CAM_SYNC_BEH/BARCODE_BUF/BARCODE_INTAN_BUF's own pins "
        f"({barcode_out_pins}) -- this would load the barcode net's own driver pin, "
        f"exactly what a dedicated leg exists to avoid",
    )
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    d43_refs = {n.ref for n in nets.get(hb_led_node, []) if values.get(n.ref) == "LED"}
    check(len(d43_refs) == 1, f"{hb_led_node}: expected exactly 1 LED, found {d43_refs}")
    d43_ref = next(iter(d43_refs))
    d43_cathode_on_dgnd = [n for n in nets.get("DGND", []) if n.ref == d43_ref and n.pin == "1"]
    check(len(d43_cathode_on_dgnd) == 1, f"{d43_ref}: cathode (pin 1) expected on DGND, not found there")
    d43_anode_on_node = [n for n in nets.get(hb_led_node, []) if n.ref == d43_ref and n.pin == "2"]
    check(len(d43_anode_on_node) == 1, f"{d43_ref}: anode (pin 2) expected on {hb_led_node!r} (in series with {r195_ref}), not found there")
    summary.append(
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        len(barcode_load_refs) == 5,
        f"BARCODE_PI: expected 5 DISTINCT load references, found {len(barcode_load_refs)}: "
        f"{barcode_load_refs} (a repeated reference would mean one 2-pin placeholder's "
        f"OWN two pins both landed on BARCODE_PI, not two independent loads)",
    )
    barcode_cathodes = [n for n in barcode_loads if (n.pinfunction or "").startswith("CATHODE")]
    check(
        not barcode_cathodes,
        f"BARCODE_PI: carries optocoupler LED cathode pin(s) "
        f"{[(n.ref, n.pin) for n in barcode_cathodes]}. This net drives 5 placeholder "
        f"headers already; an LED on top of them costs ~7.33mA on the trigger buffer's "
        f"own Y0 pin, and two of them costs 14.7mA against SN74HCT541's 6mA IOL. Each "
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    for pin, net in usb_pin_map.items():
        nodes = [n for n in nets[net] if n.ref == usb_ref and n.pin == pin]
        check(len(nodes) == 1, f"{usb_ref} pin {pin} expected on {net!r} (standard USB-A pin order), not found there: {nets[net]}")
    gnd_on_usb = [n for n in nets["DGND"] if n.ref == usb_ref and n.pin == "4"]
    check(len(gnd_on_usb) == 1, f"{usb_ref} pin 4 expected on DGND (USB-A pin 4 = GND), not found")
    summary.append(f"Internal USB header ({usb_ref}) wired in standard USB-A pin order: 1=VBUS, 2=D-, 3=D+, 4=GND.")

    # --- Every contract net this task's own net contract names (both directions) is
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    # THE central negative control this task's own brief asks for: move ONE GPIO signal
    # to a DIFFERENT (wrong) physical pin -- exactly "a wrong GPIO assignment [that]
    # would pass ERC and break PIO capture on a bench" (this file's own module
    # docstring). EVT_D5_PI (GPIO5, real position 29) moved to GPIO6's own real position
    # (31) -- both are ordinary event-data bits, so nothing else about the netlist looks
    # obviously wrong; only the physical-pin walk catches it.
    moved = copy.deepcopy(good_nets)
    idx = next(i for i, n in enumerate(moved["EVT_D5_PI"]) if n.ref == header_ref)
    old = moved["EVT_D5_PI"][idx]
    moved["EVT_D5_PI"][idx] = Node(ref=old.ref, pin=str(GPIO_PHYSICAL_PIN[6]), pinfunction=old.pinfunction, pintype=old.pintype)
    msg = _assert_fails(
        moved, good_values, "expected pin",
        "EVT_D5_PI (GPIO5) moved to GPIO6's own physical pin",
    )
    results.append(
        f"Wrong GPIO assignment (EVT_D5_PI moved from GPIO5's own physical pin 29 to "
        f"GPIO6's physical pin 31 -- ERC-invisible, bench-breaking): caught -- {msg}"
    )

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    # GND miswired: one of the 8 real GND positions (physical pin 6) reassigned to a
    # different net -- simulating a future edit that drops or mislabels a ground pin.
    # Moved to a synthetic net name no other check in verify() tracks (not a real net
    # like EVT_D2_PI, which already has its OWN header pin -- adding a second header
    # node there would trip the earlier GPIO2 walk first instead of exercising the GND
    # check this self-test targets).
    gnd_moved = copy.deepcopy(good_nets)
    gidx = next(i for i, n in enumerate(gnd_moved["DGND"]) if n.ref == header_ref and n.pin == "6")
    victim = gnd_moved["DGND"][gidx]
    gnd_moved["DGND"] = gnd_moved["DGND"][:gidx] + gnd_moved["DGND"][gidx + 1:]
    gnd_moved["STRAY_NET"] = [victim]
    msg = _assert_fails(gnd_moved, good_values, "expected DGND", "header GND pin 6 reassigned off DGND")
    results.append(f"Header GND pin (physical 6) moved off DGND: caught -- {msg}")

    # Power-pin regression: a 3V3 header pin (physical 1) accidentally bridged to this
    # board's own +3V3 rail instead of left no-connect -- exactly the "two independent
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    with_led["BARCODE_PI"] = [n for n in with_led["BARCODE_PI"] if n.ref != a_header] + [
        Node(ref="U60", pin="4", pinfunction="CATHODE2_4", pintype="passive")
    ]
    msg = _assert_fails(with_led, good_values, "carries optocoupler LED cathode pin", "an optocoupler LED cathode hung back onto BARCODE_PI")
    results.append(f"Optocoupler LED hung directly on BARCODE_PI (opto-ni's own U60 cathode, replacing a header so the load COUNT still reads 5): caught -- {msg}")

    # USB header pin-order regression: D+/D- swapped (a real, easy-to-make placement
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    results.append(f"Internal USB header D+/D- swapped ({usb_ref}): caught -- {msg}")

    # Barcode heartbeat LED collision (panel-instrumentation task, 2026-08-15): BARCODE_HB
    # accidentally shares its own trigger-buffer output pin with BARCODE_PI (simulating a
    # future edit that reuses an already-spoken-for channel instead of a genuinely spare
    # one), loading the real barcode net exactly as the dedicated leg exists to avoid.
    hb_buf_ref = next(n.ref for n in good_nets["BARCODE_HB"] if good_values.get(n.ref) == "SN74AHCT541PW")
    hb_collision = copy.deepcopy(good_nets)
    barcode_pi_out_pin = next(n.pin for n in hb_collision["BARCODE_PI"] if n.ref == hb_buf_ref and "tri_state" in n.pintype)
    hb_collision["BARCODE_HB"] = [n for n in hb_collision["BARCODE_HB"] if not (n.ref == hb_buf_ref and "tri_state" in n.pintype)] + [
        Node(ref=hb_buf_ref, pin=barcode_pi_out_pin, pinfunction=f"Y{barcode_pi_out_pin}", pintype="tri_state")
    ]
    msg = _assert_fails(hb_collision, good_values, "collides with one of", "BARCODE_HB reusing BARCODE_PI's own output pin")
    results.append(f"Barcode heartbeat LED channel collision (BARCODE_HB reusing BARCODE_PI's own {hb_buf_ref} output pin): caught -- {msg}")

    # PD1_COMP's PFI copy taking its input from the wrong net: the buffer output stays on
    # PD1_COMP_PFI_BUF, but its partner input moves off PD1_COMP onto DGND (a tied-off
    # channel's input), so the copy would carry a constant rather than the photodiode.
    miswired = copy.deepcopy(good_nets)
    out_node = next(n for n in miswired["PD1_COMP_PFI_BUF"] if "tri_state" in n.pintype)
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
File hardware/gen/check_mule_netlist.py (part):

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Also asserts (fix round 3, IMPORTANT 4) that the isolation barrier is intact at pin level:
no (ref, pin) appears on both an isolated-domain net and a non-isolated net. Pin level, not
reference level, because U5/U6 (optocouplers) and U7 (isolated DC-DC) straddle the barrier
by design -- their primary-side pins are legitimately on DGND, their secondary-side pins on
ISO_GND, and a reference-level check would incorrectly flag every one of them.

Both of the above are self-tested (see `self_test()`) against synthetic corruptions of the
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        f"{clamp_net}: clamp diode {diode_ref} has a pin on +3V3 -- regressed to the "
        f"fix-round-2 bug (see task-2-report.md, 'Fix round 2')",
    )
    check(len(on_dgnd) == 1, f"{clamp_net}: clamp diode {diode_ref} has no pin on DGND")

    # Hop 3: the SAME buffer reference's OUTPUT pin -- not just "a" tri_state driver
    # somewhere, but the one channel-paired with buf_a_pin via the 74x541 family's fixed
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        f"PI header {next(iter(pi_header_refs))}. Driver distribution: {driver_ref_counts}."
    )

    # --- BARCODE_PI: also a real physical GPIO position (GPIO17), named explicitly in
    # the brief's own Step 2 text, not just an arbitrary header pin. ---
    check("BARCODE_PI" in nets, "missing locked-contract net: 'BARCODE_PI'")
    barcode_headers = [n for n in nets["BARCODE_PI"] if not n.ref.startswith("U")]
    check(
        len(barcode_headers) == 1,
        f"BARCODE_PI: expected exactly 1 header-pin node, found {nets['BARCODE_PI']}",
    )
    check(
        barcode_headers[0].pin == str(BARCODE_GPIO_PHYSICAL_PIN),
        f"BARCODE_PI: lands on header pin {barcode_headers[0]}, expected physical pin "
        f"{BARCODE_GPIO_PHYSICAL_PIN} (the real Pi GPIO17 position)",
    )
    summary.append(
        f"BARCODE_PI lands on {barcode_headers[0].ref}.{barcode_headers[0].pin}, the real "
        f"Pi GPIO17 physical position."
    )

    # --- Isolation barrier: no (ref, pin) may appear on both an isolated-domain net and a
    # non-isolated net (fix round 3, IMPORTANT 4). Pin level, not reference level -- U5,
    # U6 (optocouplers) and U7 (isolated DC-DC) straddle the barrier BY DESIGN (LED/
    # primary-side pins legitimately on DGND, output/secondary-side pins legitimately on
    # ISO_GND); a reference-level check would incorrectly flag every one of them. ---
    for name in ISO_NETS + NON_ISO_NETS:
        check(name in nets, f"missing net: {name!r}")
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
    # IMPORTANT 3 negative control: swap two channels' buffer OUTPUT pins (a permutation)
    # and confirm the end-to-end walk catches it. Channels 3 and 5 are both "direct"
    # lines (not GPIO0/1's indirect resistor-bridged pair), so EVT_D3_PI and EVT_D5_PI
    # each hold exactly one tri_state driver node -- swap those two Node objects between
    # the two nets.
    swapped = copy.deepcopy(good_nets)
    d3_driver_idx = next(i for i, n in enumerate(swapped["EVT_D3_PI"]) if "tri_state" in n.pintype)
    d5_driver_idx = next(i for i, n in enumerate(swapped["EVT_D5_PI"]) if "tri_state" in n.pintype)
    swapped["EVT_D3_PI"][d3_driver_idx], swapped["EVT_D5_PI"][d5_driver_idx] = (
        swapped["EVT_D5_PI"][d5_driver_idx],
        swapped["EVT_D3_PI"][d3_driver_idx],
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    msg = _assert_fails(swapped, "permuted", "channel 3/5 buffer-output swap")
    results.append(f"Channel permutation (swapped EVT_D3_PI/EVT_D5_PI buffer drivers): caught -- {msg}")

    # IMPORTANT 4 negative control: short ISO_GND to DGND (a single shared pin) and
    # confirm the isolation-barrier check catches it.
    shorted = copy.deepcopy(good_nets)
    phantom = Node(ref="DBG99", pin="1", pinfunction="", pintype="passive")
    shorted["ISO_GND"] = shorted["ISO_GND"] + [phantom]
    shorted["DGND"] = shorted["DGND"] + [phantom]
    msg = _assert_fails(shorted, "isolation barrier violated", "ISO_GND/DGND short")
    results.append(f"Isolation barrier short (ISO_GND tied to DGND via one shared pin): caught -- {msg}")

    # Bypass-cap negative control: drop one capacitor's two nodes from ISO_5V/ISO_GND
    # (simulating an accidental deletion of a decoupling cap in a future edit) and confirm
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
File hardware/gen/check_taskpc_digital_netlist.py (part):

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        f"LVC input to the 3.3V rail (see bidirectional_clamp()'s own docstring for why "
        f"this is wrong -- the exact mule-board fix-round-2 defect)",
    )
    check(len(on_dgnd) == 1, f"{clamp_net}: clamp diode {diode_ref} has no pin on DGND")

    # Hop 3: the buffer-input nodes -- one LVC541 (the +3V3 bank) and one HCT541 (the +5V
    # _BUF bank), identified by Value (not by reference number, which this checker does
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    # OR gate's own second input (RWD_BTN_PULSE, just confirmed above) -- "the one-shot
    # exists between button and OR", made executable. Real pin map (verified against the
    # real datasheet -- see gen_breakout_taskpc_digital.py's own place_reward_oneshot()
    # docstring): pin1(A)->DGND, pin2(B)->RWD_BTN_DEB (trigger), pin3(Clr)->+5V (never
    # reset), pin13(Q)->RWD_BTN_PULSE (active-HIGH, same polarity RWD_BTN_DEB already
    # has -- see the same-polarity check below). ---
    oneshot_refs = {n.ref for n in nets.get("RWD_BTN_PULSE", []) if values.get(n.ref) == "74HCT123D"}
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    check(len(oneshot_q) == 1 and oneshot_q[0].pin == "13", f"RWD_BTN_PULSE: expected {oneshot_ref} pin 13 (Q), found {oneshot_q}")
    oneshot_b = [n for n in nets.get("RWD_BTN_DEB", []) if n.ref == oneshot_ref]
    check(len(oneshot_b) == 1 and oneshot_b[0].pin == "2", f"RWD_BTN_DEB: expected {oneshot_ref} pin 2 (B, trigger), found {oneshot_b}")
    oneshot_a = [n for n in nets.get("DGND", []) if n.ref == oneshot_ref and n.pin == "1"]
    check(len(oneshot_a) == 1, f"{oneshot_ref} pin 1 (A) expected on DGND (tied permanently low), not found")
    oneshot_clr = [n for n in nets.get("+5V", []) if n.ref == oneshot_ref and n.pin == "3"]
    check(len(oneshot_clr) == 1, f"{oneshot_ref} pin 3 (RD-bar/Clr) expected on +5V (never reset), not found")
    # Rext/Cext: pin15 (REXT/CEXT, shared node with Rext's own far end on +5V) and pin14
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    check(
        btn_hdr_refs == {n.ref for n in nets["DGND"] if n.ref in btn_hdr_refs},
        f"RWD_BTN's own button/jack connector(s) {btn_hdr_refs} should each also have a "
        f"pin on DGND (the switch's other terminal)",
    )
    check(len(btn_hdr_refs) == 2, f"RWD_BTN: expected 2 connectors (panel button + remote jack), found {btn_hdr_refs}")

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            )
            shell = BNC_PORT_SHELL[centre]
            check(
                any(n.ref == ref and n.pin == shell for n in nets.get("DGND", [])),
                f"{ref} port {centre}/{shell} ({label}): this port's own shell is not on DGND",
            )
            reward_ports[net] = (ref, centre)
        check(
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    # --- No unused logic-gate input left floating: every unused gate of U8 (74HCT32,
    # gates 2-4) and the debounce IC (74HCT14, gates 3-6) has both/its own input tied to
    # DGND. Discovered from the used gates' own refs above rather than assumed. ---
    or_dgnd_pins = sorted((int(p) for r, p in _pins_on(nets, "DGND") if r == or_ref))
    check(
        set(or_dgnd_pins) >= {4, 5, 7, 9, 10, 12, 13},
        f"{or_ref} (74HCT32): expected unused-gate inputs {{4,5,9,10,12,13}} plus GND(7) "
        f"tied to DGND, found {or_dgnd_pins}",
    )
    deb_dgnd_pins = sorted((int(p) for r, p in _pins_on(nets, "DGND") if r == deb_ref))
    check(
        set(deb_dgnd_pins) >= {3, 5, 7, 9, 11, 13},
        f"{deb_ref} (74HCT14): expected unused-gate inputs {{3,5,9,11,13}} (5 unused "
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        f"that drives it, found {nets.get('PD1_COMP_PFI_BUF')}",
    )
    check(values.get(PFI_SERIES) == "100", f"{PFI_SERIES}: expected 100 ohm, found {values.get(PFI_SERIES)!r}")
    conn0_dgnd = {n.pin for n in nets.get("DGND", []) if n.ref == conn0_ref}
    check(
        not conn0_dgnd,
        f"Connector 0 ({conn0_ref}) has pin(s) {sorted(conn0_dgnd)} on DGND. Its AISENSE is "
        f"on AGND, so that makes it a second component on both grounds after the star "
        f"point's net tie -- decision D3, reversed 2026-10-18 for exactly this reason",
    )
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    # SAME package, channel-local, which is the harder case: a same-package permutation,
    # not just a cross-package one).
    swapped_pi = copy.deepcopy(good_nets)
    d3_idx = next(i for i, n in enumerate(swapped_pi["EVT_D3_PI"]) if "tri_state" in n.pintype)
    d5_idx = next(i for i, n in enumerate(swapped_pi["EVT_D5_PI"]) if "tri_state" in n.pintype)
    swapped_pi["EVT_D3_PI"][d3_idx], swapped_pi["EVT_D5_PI"][d5_idx] = (
        swapped_pi["EVT_D5_PI"][d5_idx], swapped_pi["EVT_D3_PI"][d3_idx],
    )
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        swapped_mdr["EVT_D4_TPC"][d4_hdr_idx], swapped_mdr["EVT_D2_TPC"][d2_hdr_idx],
    )
    msg = _assert_fails(swapped_mdr, good_values, "expected pin", "channel 2/4 Connector-1 pin swap")
    results.append(f"MDR68 physical-pin permutation (EVT_D2_TPC/EVT_D4_TPC Connector-1 pins swapped): caught -- {msg}")

    # Clamp rail regression: one channel's clamp diode gains a pin on +3V3 -- the exact
    # mule-board fix-round-2 defect this design must not repeat.
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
